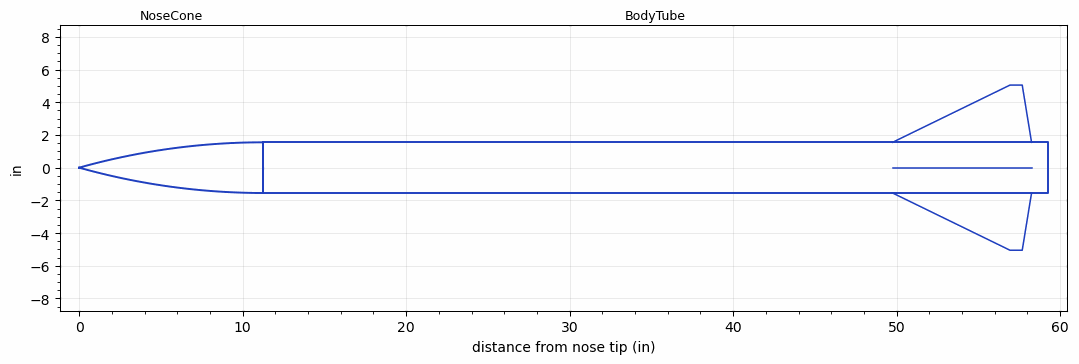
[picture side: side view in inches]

<RASAeroDocument>
 <FileVersion>2</FileVersion>
 <RocketDesign>
  <NoseCone>
   <Length>11.25</Length>
   <Diameter>3.1</Diameter>
   <Shape>Tangent Ogive</Shape>
   <Location>0</Location>
  </NoseCone>
  <BodyTube>
   <Length>48</Length>
   <Diameter>3.1</Diameter>
   <RailGuideDiameter>0.375</RailGuideDiameter>
   <RailGuideHeight>0.3438</RailGuideHeight>
   <Location>11.25</Location>
   <Fin>
    <Count>4</Count>
    <Chord>8.5</Chord>
    <Span>3.5</Span>
    <SweepDistance>7.18</SweepDistance>
    <TipChord>0.75</TipChord>
    <Thickness>0.125</Thickness>
    <Location>9.5</Location>
    <AirfoilSection>Hexagonal</AirfoilSection>
    <FX1>0.4375</FX1>
    <FX3>0.25</FX3>
   </Fin>
  </BodyTube>
  <Surface>Smooth (Zero Roughness)</Surface>
  <ModifiedBarrowman>False</ModifiedBarrowman>
  <Turbulence>False</Turbulence>
  <SustainerNozzle>0.63</SustainerNozzle>
  <UseBooster1>False</UseBooster1>
  <UseBooster2>False</UseBooster2>
  <Comments>2004 Aerospace Vehicle Test Course at USAF Test Pilot School
Team 3 Rocket
AltAcc Altimeter
Barometric Altitude = 3964 ft

RASAero II Prediction = 3876 ft
Error = -2.22%
</Comments>
 </RocketDesign>
 <LaunchSite>
  <Altitude>2302</Altitude>
  <Pressure>0</Pressure>
  <RodAngle>3</RodAngle>
  <RodLength>10</RodLength>
  <Temperature>77</Temperature>
  <WindSpeed>0</WindSpeed>
 </LaunchSite>
 <Recovery>
  <Altitude1>1000</Altitude1>
  <Altitude2>1000</Altitude2>
  <DeviceType1>Parachute</DeviceType1>
  <DeviceType2>Chute</DeviceType2>
  <Event1>True</Event1>
  <Event2>False</Event2>
  <Size1>36</Size1>
  <Size2>100</Size2>
  <EventType1>Apogee</EventType1>
  <EventType2>None</EventType2>
  <CD1>1.33</CD1>
  <CD2>1.33</CD2>
 </Recovery>
 <SimulationList>
  <Simulation>
   <SustainerEngine>I205  (CTI)</SustainerEngine>
   <SustainerLaunchWt>3.41</SustainerLaunchWt>
   <SustainerNozzleDiameter>0.63</SustainerNozzleDiameter>
   <SustainerCG>40</SustainerCG>
   <SustainerIgnitionDelay>0</SustainerIgnitionDelay>
   <Booster1SeparationDelay>0</Booster1SeparationDelay>
   <Booster1IgnitionDelay>0</Booster1IgnitionDelay>
   <IncludeBooster1>False</IncludeBooster1>
   <Booster2Delay>0</Booster2Delay>
   <IncludeBooster2>False</IncludeBooster2>
   <TimetoApogee>14.11023</TimetoApogee>
   <MaxAltitude>3875.957</MaxAltitude>
   <MaxVelocity>723.2623</MaxVelocity>
  </Simulation>
 </SimulationList>
</RASAeroDocument>
